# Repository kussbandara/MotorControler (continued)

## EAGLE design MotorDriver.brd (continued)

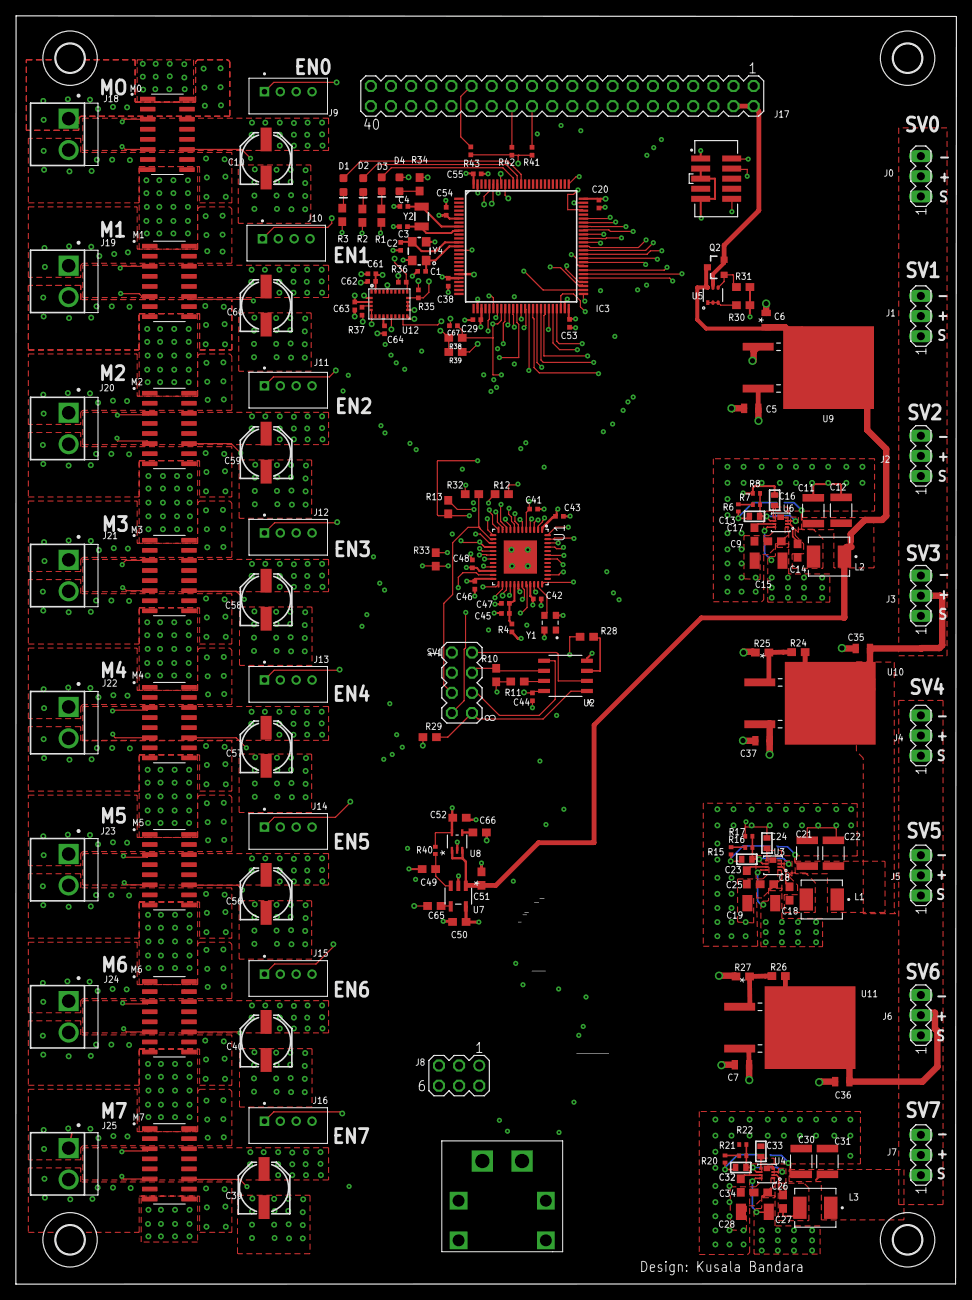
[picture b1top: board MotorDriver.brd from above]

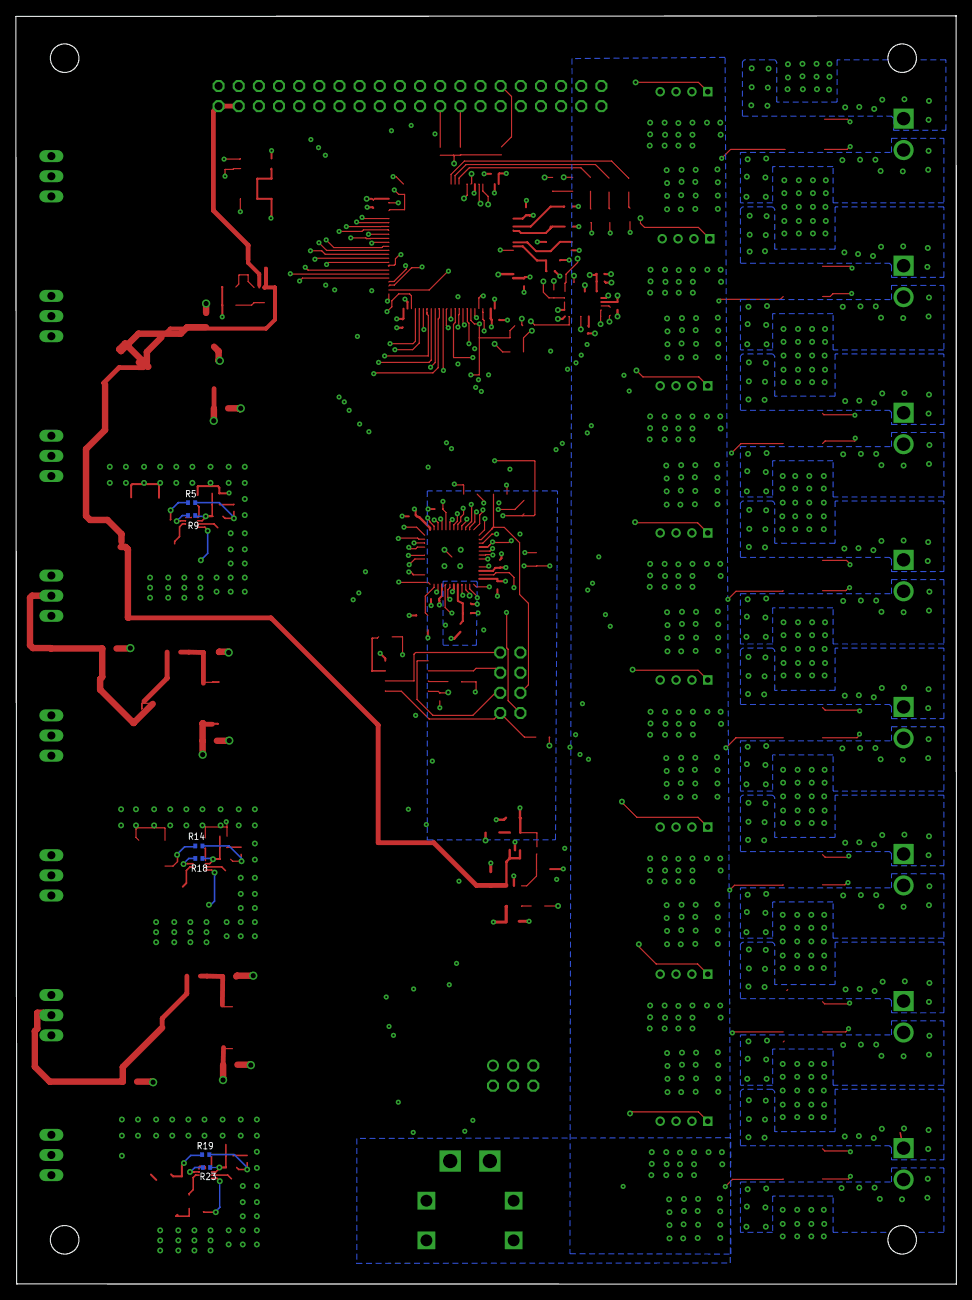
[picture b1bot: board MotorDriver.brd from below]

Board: 6 copper layers, 118.6 x 159.9 mm, 175 parts (6 on the bottom side), 150 nets.

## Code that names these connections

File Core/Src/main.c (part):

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      LL_TIM_OC_SetCompareCH1(TIM3,value);
      
      if (dir==0){
        //Motor 0=> IN1- PD14, IN2- PD15, PWM1 pin PC6
        //Motor backward
        GPIOD->BSRR = LL_GPIO_PIN_14;
        GPIOD->BRR = LL_GPIO_PIN_15;
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   if (motorNo==1){
      LL_TIM_OC_SetCompareCH2(TIM3,value);
      if (dir==0){
        //Motor 1=> IN1- PD12, IN2- PD13, PWM1 pin PC7
        //Motor backward
        GPIOD->BSRR = LL_GPIO_PIN_12;
        GPIOD->BRR = LL_GPIO_PIN_13;
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   if (motorNo==2){
         LL_TIM_OC_SetCompareCH3(TIM3,value);
      if (dir==0){
        //Motor 2=> IN1- PA8 , IN2- PA9, PWM1 pin PC8
        //Motor backward
        GPIOA->BSRR = LL_GPIO_PIN_8;
        GPIOA->BRR = LL_GPIO_PIN_9;
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   if(motorNo==3){
        LL_TIM_OC_SetCompareCH4(TIM3,value);
      if (dir==0){
        //Motor 3=> IN1- PA10 , IN2- PA11, PWM1 pin PC8
        //Motor backward
        GPIOA->BSRR = LL_GPIO_PIN_11;
        GPIOA->BRR = LL_GPIO_PIN_10;
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   if(motorNo==4){
       LL_TIM_OC_SetCompareCH1(TIM1,value);
      if (dir==0){
        //Motor 4=> IN1- PB2 , IN2- PB1, PWM1 pin PE9
        //Motor backward
        GPIOB->BSRR = LL_GPIO_PIN_2;
        GPIOB->BRR = LL_GPIO_PIN_1;
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       LL_TIM_OC_SetCompareCH2(TIM1,value);
       
      if (dir==0){
        //Motor 5=> IN1- PE8 , IN2- PE7, PWM1 pin PE11
        //Motor backward
        GPIOE->BSRR = LL_GPIO_PIN_8;
        GPIOE->BRR = LL_GPIO_PIN_7;
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   if(motorNo==6){
       LL_TIM_OC_SetCompareCH3(TIM1,value);
      if (dir==0){
        //Motor 4=> IN1- PE12 , IN2- PE10, PWM1 pin PE13
        //Motor backward
        GPIOE->BSRR = LL_GPIO_PIN_12;
        GPIOE->BRR = LL_GPIO_PIN_10;
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   if(motorNo==7){
       LL_TIM_OC_SetCompareCH4(TIM1,value);
      if (dir==0){
        //Motor 4=> IN1- PB10 , IN2- PE15, PWM1 pin PE14
        //Motor backward
        GPIOB->BSRR = LL_GPIO_PIN_10;
        GPIOE->BRR = LL_GPIO_PIN_15;
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
  LL_AHB1_GRP1_EnableClock(LL_AHB1_GRP1_PERIPH_GPIOA);
  /**SPI1 GPIO Configuration
  PA5   ------> SPI1_SCK
  PA6   ------> SPI1_MISO
  PA7   ------> SPI1_MOSI
  PB0 -----> SPI1_CS
  */
  GPIO_InitStruct.Pin = LL_GPIO_PIN_5;
  GPIO_InitStruct.Mode = LL_GPIO_MODE_ALTERNATE;
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
  LL_AHB1_GRP1_EnableClock(LL_AHB1_GRP1_PERIPH_GPIOB);
  /**SPI2 GPIO Configuration
  PB13   ------> SPI2_SCK
  PB14   ------> SPI2_MISO
  PB15   ------> SPI2_MOSI
  */
  GPIO_InitStruct.Pin = LL_GPIO_PIN_13;
  GPIO_InitStruct.Mode = LL_GPIO_MODE_ALTERNATE;
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
  LL_AHB1_GRP1_EnableClock(LL_AHB1_GRP1_PERIPH_GPIOB);
  /**I2C1 GPIO Configuration
  PB8   ------> I2C1_SCL
  PB9   ------> I2C1_SDA
  */
  GPIO_InitStruct.Pin = LL_GPIO_PIN_8;
  GPIO_InitStruct.Mode = LL_GPIO_MODE_ALTERNATE;
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  /* USER CODE END TIM1_Init 2 */
  LL_AHB1_GRP1_EnableClock(LL_AHB1_GRP1_PERIPH_GPIOE);
  /**TIM1 GPIO Configuration
  PE9   ------> TIM1_CH1        Motor 4
  PE11   ------> TIM1_CH2       Motor 5
  PE13   ------> TIM1_CH3       Motor 6
  PE14   ------> TIM1_CH4       Motor 7
  */
  GPIO_InitStruct.Pin = LL_GPIO_PIN_9;
  GPIO_InitStruct.Mode = LL_GPIO_MODE_ALTERNATE;
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  LL_TIM_SetTriggerOutput(TIM3, LL_TIM_TRGO_RESET);
  LL_TIM_DisableMasterSlaveMode(TIM3);
  
   //Motor 0-PC6
  LL_TIM_OC_EnablePreload(TIM3, LL_TIM_CHANNEL_CH1);
  TIM_OC_InitStruct.OCMode = LL_TIM_OCMODE_PWM2;
  TIM_OC_InitStruct.OCState = LL_TIM_OCSTATE_DISABLE;
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  LL_TIM_OC_DisableFast(TIM3, LL_TIM_CHANNEL_CH1);
  LL_TIM_CC_EnableChannel(TIM3,  LL_TIM_CHANNEL_CH1); 
  
   //Motor 1-PC7
  LL_TIM_OC_EnablePreload(TIM3, LL_TIM_CHANNEL_CH2);
  TIM_OC_InitStruct.OCState = LL_TIM_OCSTATE_DISABLE;
  TIM_OC_InitStruct.OCNState = LL_TIM_OCSTATE_DISABLE;
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  LL_TIM_OC_DisableFast(TIM3, LL_TIM_CHANNEL_CH2);
  LL_TIM_CC_EnableChannel(TIM3,  LL_TIM_CHANNEL_CH2); 
  
   //Motor 2-PC8
  LL_TIM_OC_EnablePreload(TIM3, LL_TIM_CHANNEL_CH3);
  TIM_OC_InitStruct.OCState = LL_TIM_OCSTATE_DISABLE;
  TIM_OC_InitStruct.OCNState = LL_TIM_OCSTATE_DISABLE;
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  LL_TIM_OC_DisableFast(TIM3, LL_TIM_CHANNEL_CH3);
  LL_TIM_CC_EnableChannel(TIM3,  LL_TIM_CHANNEL_CH3); 
  
   //Motor 3-PC9
  LL_TIM_OC_EnablePreload(TIM3, LL_TIM_CHANNEL_CH4);
  TIM_OC_InitStruct.OCState = LL_TIM_OCSTATE_DISABLE;
  TIM_OC_InitStruct.OCNState = LL_TIM_OCSTATE_DISABLE;
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  LL_AHB1_GRP1_EnableClock(LL_AHB1_GRP1_PERIPH_GPIOC);

  /**TIM3 GPIO Configuration
  PC6   ------> TIM3_CH1
  PC7   ------> TIM3_CH2
  PC8   ------> TIM3_CH3
  PC9   ------> TIM3_CH4
  */
  GPIO_InitStruct.Pin = LL_GPIO_PIN_6;
  GPIO_InitStruct.Mode = LL_GPIO_MODE_ALTERNATE;
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
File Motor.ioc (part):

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Mcu.Name=STM32F071V(8-B)Tx
Mcu.Package=LQFP100
Mcu.UserName=STM32F071V8Tx
PA10.Signal=GPIO_Output
PA11.Signal=GPIO_Output
PA5.Mode=Full_Duplex_Master
PA5.Signal=SPI1_SCK
PA6.Mode=Full_Duplex_Master
PA6.Signal=SPI1_MISO
PA7.Mode=Full_Duplex_Master
PA7.Signal=SPI1_MOSI
PA8.Signal=GPIO_Output
PA9.Signal=GPIO_Output
PB1.Signal=GPIO_Output
PB10.Signal=GPIO_Output
PB13.Mode=Full_Duplex_Slave
PB13.Signal=SPI2_SCK
PB14.Mode=Full_Duplex_Slave
PB14.Signal=SPI2_MISO
PB15.Mode=Full_Duplex_Slave
PB15.Signal=SPI2_MOSI
PB2.Signal=GPIO_Output
PC6.Signal=S_TIM3_CH1
PC7.Signal=S_TIM3_CH2
PC8.Signal=S_TIM3_CH3
PC9.Signal=S_TIM3_CH4
PD12.Signal=GPIO_Output
PD13.Signal=GPIO_Output
PD14.Signal=GPIO_Output
PD15.Signal=GPIO_Output
PE10.Signal=GPIO_Output
PE11.Signal=S_TIM1_CH2
PE12.Signal=GPIO_Output
PE13.Signal=S_TIM1_CH3
PE14.Signal=S_TIM1_CH4
PE15.Signal=GPIO_Output
PE7.Signal=GPIO_Output
PE8.Signal=GPIO_Output
PE9.Signal=S_TIM1_CH1
PF0-OSC_IN.Mode=HSE-External-Oscillator
PF0-OSC_IN.Signal=RCC_OSC_IN
PF1-OSC_OUT.Mode=HSE-External-Oscillator
PF1-OSC_OUT.Signal=RCC_OSC_OUT
RCC.HSE_VALUE=16000000
RCC.SYSCLKFreq_VALUE=48000000
RCC.SYSCLKSource=RCC_SYSCLKSOURCE_PLLCLK
board=custom

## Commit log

2020-07-28 Update MotorDriver.sch
    updates
2020-07-31 Update MotorDriver.sch
    updated-7/31
2020-08-06 added brd file
2021-01-05 adding FPGA files
2021-01-05 adding files
2021-01-05 removed attibutes
2021-01-07 adding iar files
2021-01-07 Adding Eagle Files
2021-01-07 adding test file
